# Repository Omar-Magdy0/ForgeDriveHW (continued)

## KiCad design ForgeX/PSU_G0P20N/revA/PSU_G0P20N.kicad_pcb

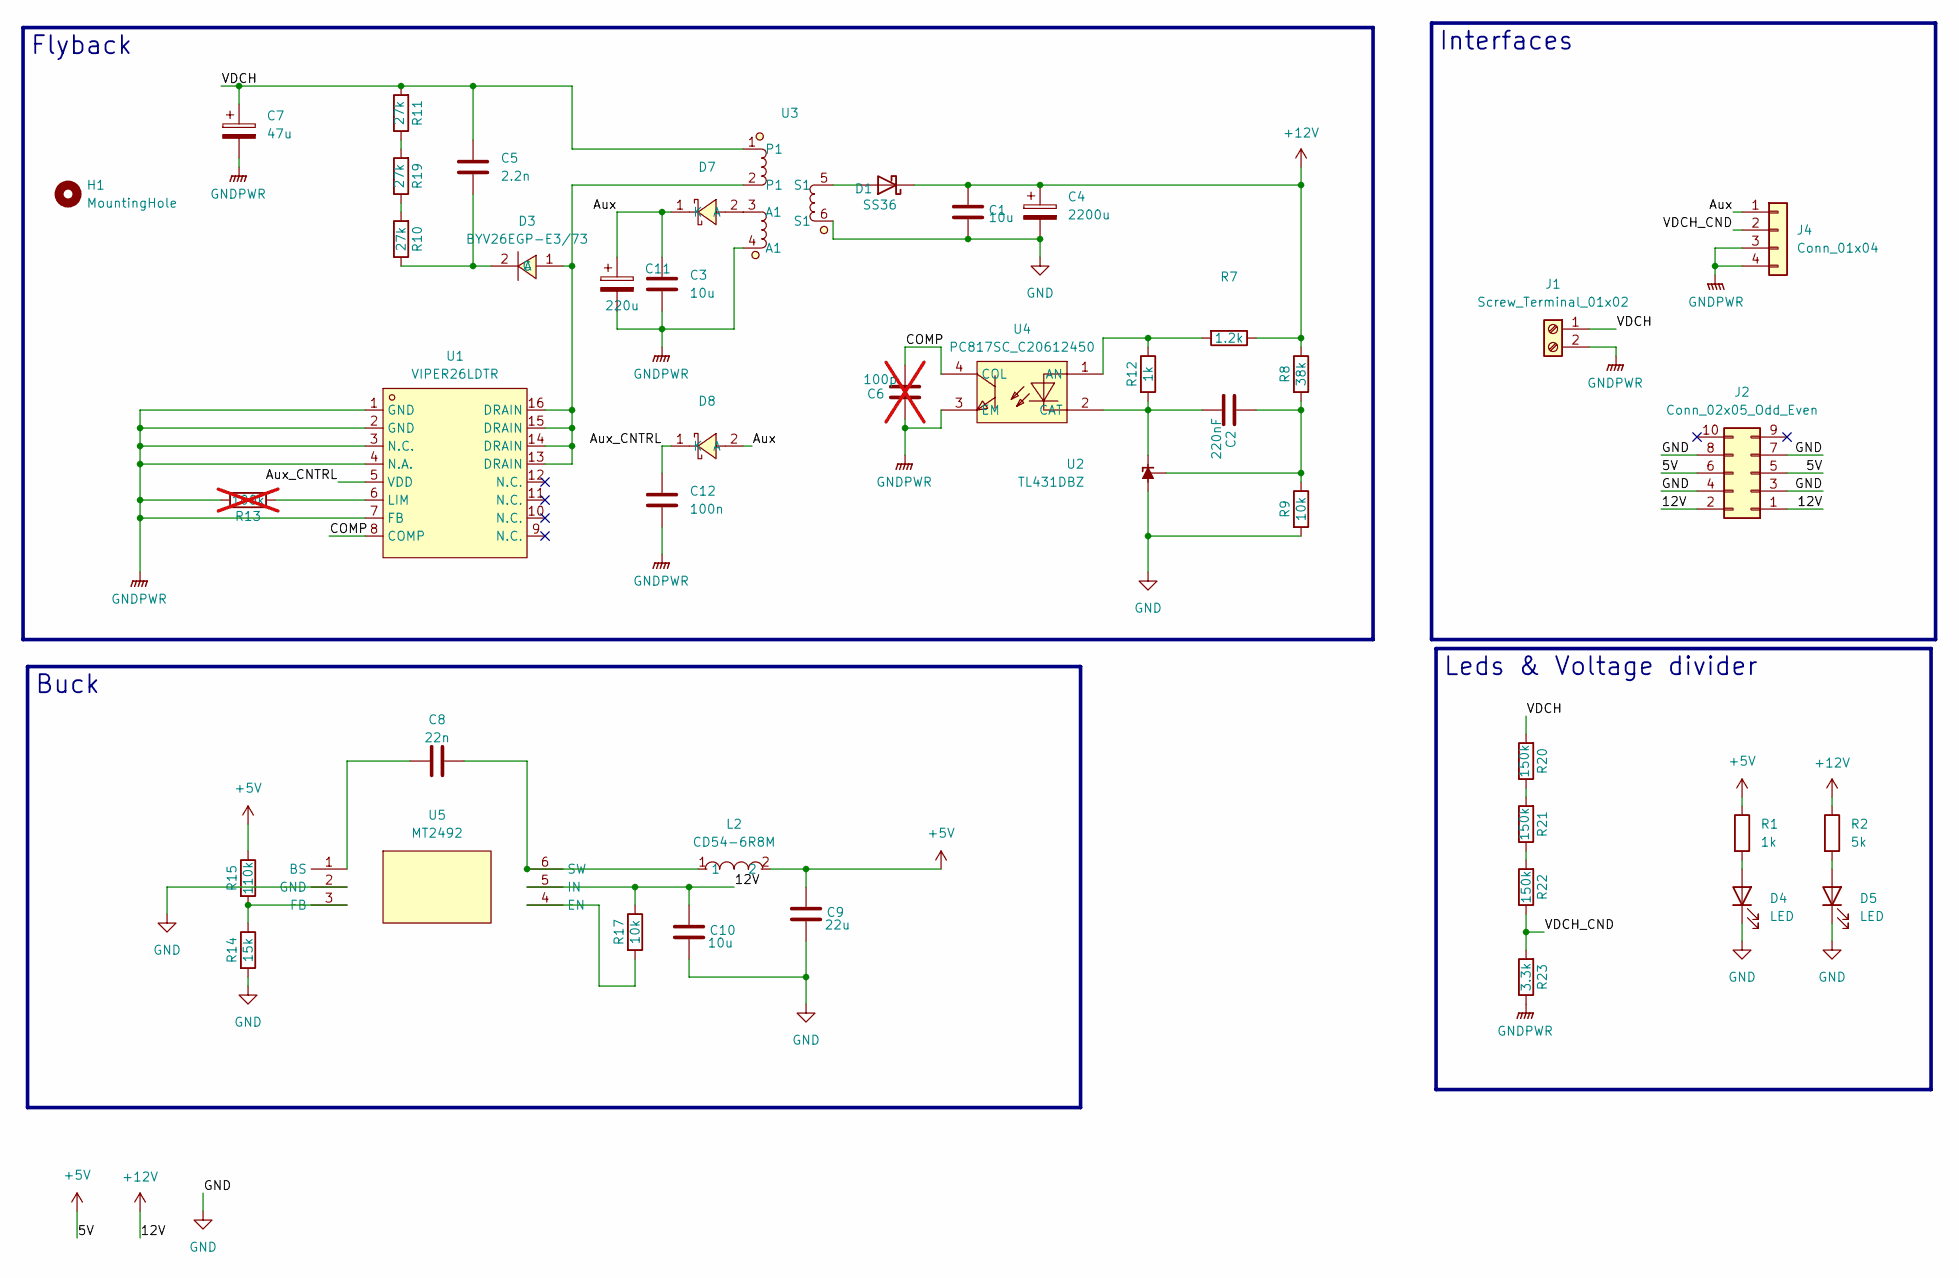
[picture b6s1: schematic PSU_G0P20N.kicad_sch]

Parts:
C1, C3, C10: 10u; C_1206_3216Metric_Pad1.33x1.80mm_HandSolder
C2: 220nF; C_0603_1608Metric_Pad1.08x0.95mm_HandSolder
C4: 2200u; CP_Radial_D10.0mm_P5.00mm
C5: 2.2n; C_Disc_D5.0mm_W2.5mm_P5.00mm
C6: 100p; C_0603_1608Metric_Pad1.08x0.95mm_HandSolder; not fitted
C7: 47u; CP_Radial_D10.0mm_P7.50mm
C8: 22n; C_0603_1608Metric_Pad1.08x0.95mm_HandSolder
C9: 22u; C_1206_3216Metric_Pad1.33x1.80mm_HandSolder
C11: 220u; CP_Radial_D6.3mm_P2.50mm
C12: 100n; C_0603_1608Metric_Pad1.08x0.95mm_HandSolder
D1: SS36; D_SMA
D3: BYV26EGP-E3/73; DO-15_BD3.1-L6.7-P10.70-D0.9-FD; MPN BYV26EGP-E3/73; LCSC Part C15074
D4, D5: LED; LED_1206_3216Metric_Pad1.42x1.75mm_HandSolder
D7, D8: SD103AWS_C5345966; SOD-323_L1.7-W1.3-LS2.5-RD; MPN SD103AWS; LCSC Part C5345966
H1: MountingHole; MountingHole_2.1mm
J1: Screw_Terminal_01x02; SPACER_M3_PCONN_PSU
J2: Conn_02x05_Odd_Even; PinHeader_2x05_P2.54mm_Vertical
J4: Conn_01x04; JST_XH_B4B-XH-A_1x04_P2.50mm_Vertical
L2: CD54-6R8M; IND-SMD_L5.8-W5.2_CD54; MPN CD54-6R8M; LCSC Part C7588992
R1: 1k; R_1206_3216Metric_Pad1.30x1.75mm_HandSolder
R2: 5k; R_1206_3216Metric_Pad1.30x1.75mm_HandSolder
R7: 1.2k; R_0603_1608Metric_Pad0.98x0.95mm_HandSolder
R8: 38k; R_0603_1608Metric_Pad0.98x0.95mm_HandSolder
R9, R17: 10k; R_0603_1608Metric_Pad0.98x0.95mm_HandSolder
R10, R11, R19: 27k; R_1206_3216Metric
R12: 1k; R_0603_1608Metric_Pad0.98x0.95mm_HandSolder
R13: 100k; R_0603_1608Metric_Pad0.98x0.95mm_HandSolder; not fitted
R14: 15k; R_0603_1608Metric_Pad0.98x0.95mm_HandSolder
R15: 110k; R_0603_1608Metric_Pad0.98x0.95mm_HandSolder
R20, R21, R22: 150k; R_1206_3216Metric
R23: 3.3k; R_0603_1608Metric_Pad0.98x0.95mm_HandSolder
U1: VIPER26LDTR; SOIC-16_L9.9-W3.9-P1.27-LS6.0-BL; MPN VIPER26LDTR; LCSC Part C134483
U2: TL431DBZ; SOT-23
U3: E22 Trans
U4: PC817SC_C20612450; OPTO-SMD-4_L4.6-W6.5-P2.54-LS10.3-TL; MPN PC817SC; LCSC Part C20612450
U5: MT2492; SOT-23-6_L2.9-W1.6-P0.95-LS2.8-BL_3; MPN MT2492; LCSC Part C89358

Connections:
+5V: C9.1, J2.5, J2.6, L2.2, R1.1, R15.1
+12V: C1.1, C4.1, C10.1, D1.1 (K), J2.1, J2.2, R2.1, R7.1, R8.1, R17.1, U5.5 (IN)
/Aux: C3.1, C11.1, D7.1 (K), D8.2 (A), J4.1
/Aux_CNTRL: C12.1, D8.1 (K), U1.5 (VDD)
/COMP: C6.2, U1.8 (COMP), U4.4 (COL)
/VDCH: C5.1, C7.1, J1.1, R11.2, R20.2, U3.1
/VDCH_CND: J4.2, R22.1, R23.2
GND: C1.2, C4.2, C9.2, C10.2, D4.1 (K), D5.1 (K), J2.3, J2.4, J2.7, J2.8, R9.2, R14.2, U2.3 (A), U3.6 (S1), U5.2 (GND)
GNDPWR: C3.2, C6.1, C7.2, C11.2, C12.2, J1.2, J4.3, J4.4, R13.1, R23.1, U1.1 (GND), U1.2 (GND), U1.3 (N.C.), U1.4 (N.A.), U1.7 (FB), U3.4 (A1), U4.3 (EM)
unnamed: D1.2 (A), U3.5 (S1)
unnamed: D3.1 (A), U1.13 (DRAIN), U1.14 (DRAIN), U1.15 (DRAIN), U1.16 (DRAIN), U3.2 (P1)
unnamed: C5.2, D3.2 (C), R10.1
unnamed: D4.2 (A), R1.2
unnamed: D5.2 (A), R2.2
unnamed: D7.2 (A), U3.3 (A1)
unnamed: R10.2, R19.1
unnamed: R11.1, R19.2
unnamed: R20.1, R21.2
unnamed: R21.1, R22.2
unnamed: R13.2, U1.6 (LIM)
unnamed: C2.2, R12.2, U2.1 (K), U4.2 (CAT)
unnamed: C2.1, R8.2, R9.1, U2.2 (REF)
unnamed: R7.2, R12.1, U4.1 (AN)
unnamed: C8.2, U5.1 (BS)
unnamed: R17.2, U5.4 (EN)
unnamed: R14.1, R15.2, U5.3 (FB)
unnamed: C8.1, L2.1, U5.6 (SW)

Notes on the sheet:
Flyback
Buck
Interfaces
Leds & Voltage divider

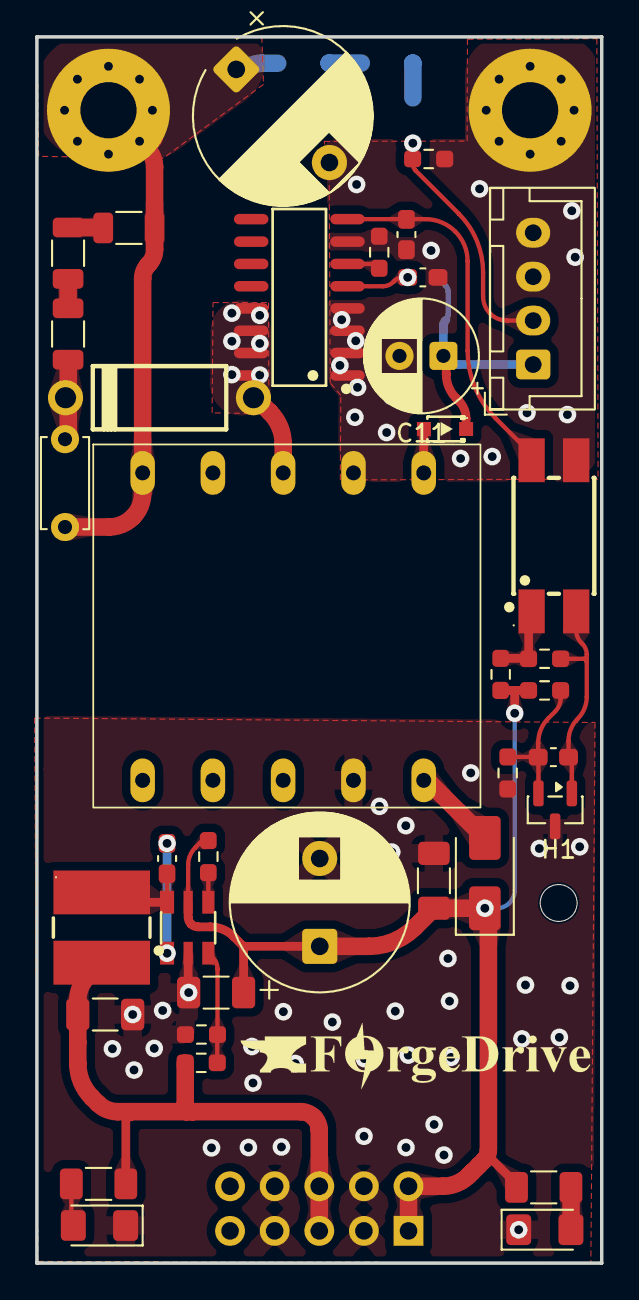
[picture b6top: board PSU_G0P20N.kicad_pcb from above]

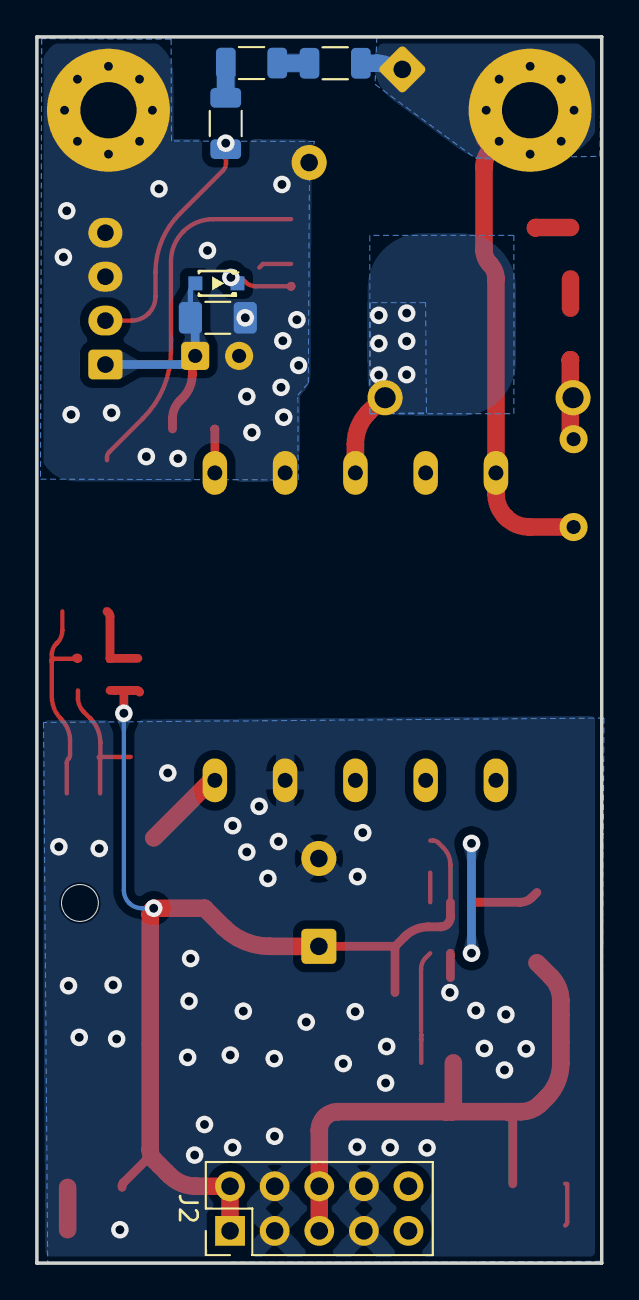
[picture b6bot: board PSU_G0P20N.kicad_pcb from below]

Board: 2 copper layers, 32.1 x 69.8 mm, 45 parts (6 on the bottom side), 27 nets.

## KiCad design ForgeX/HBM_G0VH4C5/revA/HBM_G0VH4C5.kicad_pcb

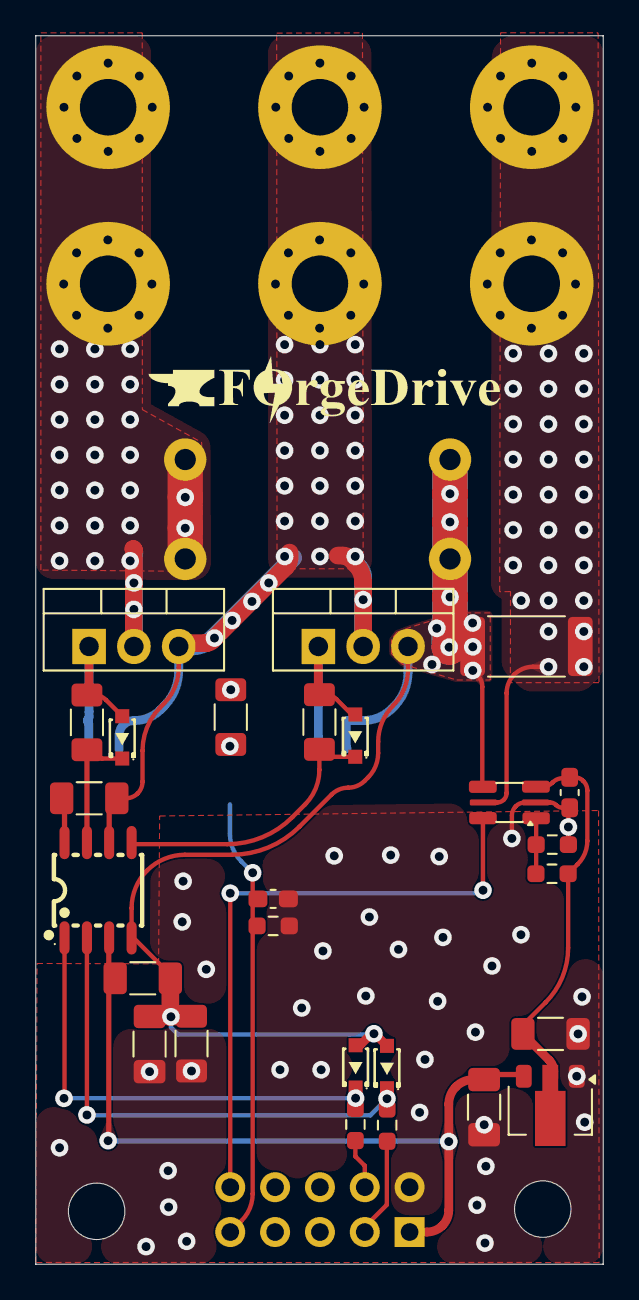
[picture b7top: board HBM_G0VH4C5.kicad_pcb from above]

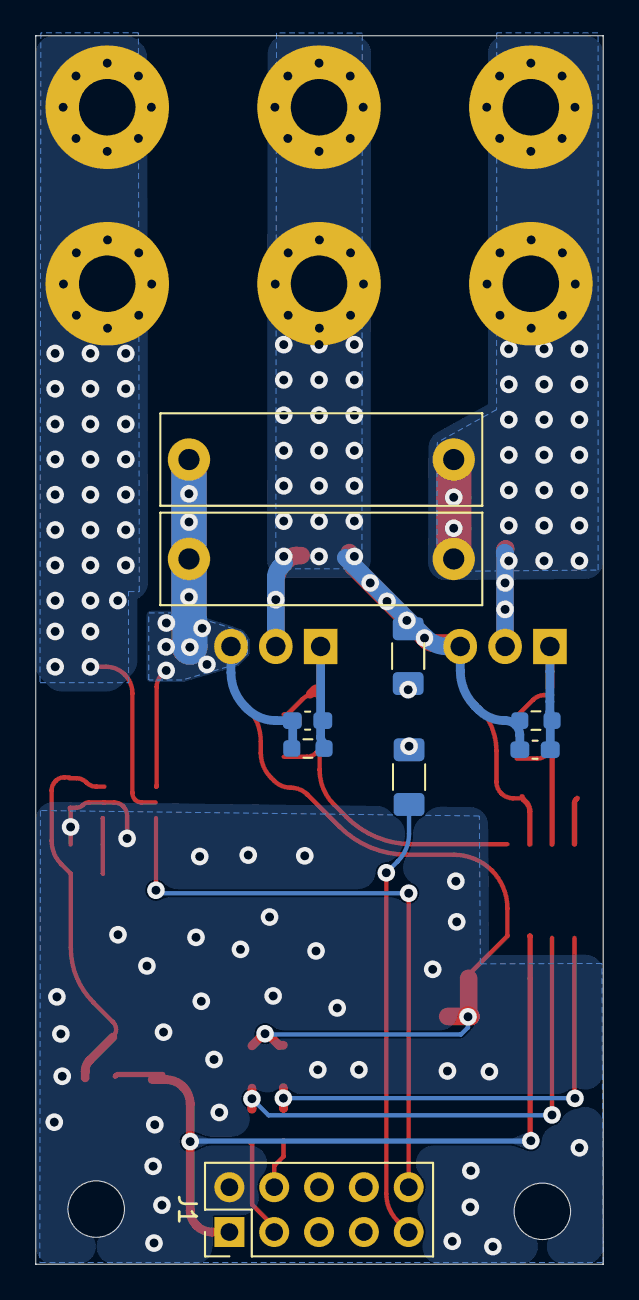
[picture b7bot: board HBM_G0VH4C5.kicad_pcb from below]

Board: 2 copper layers, 32.2 x 69.6 mm, 38 parts (9 on the bottom side), 21 nets.

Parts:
C2, C3: 1n; C_0603_1608Metric_Pad1.08x0.95mm_HandSolder
C4: 0.1u; C_0603_1608Metric_Pad1.08x0.95mm_HandSolder
C7: 10uF; C_1206_3216Metric_Pad1.33x1.80mm_HandSolder
C8: 1u; C_1206_3216Metric_Pad1.33x1.80mm_HandSolder
C9: 47n; C_0603_1608Metric_Pad1.08x0.95mm_HandSolder
C10: 100p; C_1206_3216Metric_Pad1.33x1.80mm_HandSolder
C20, C21: 1u; C_Rect_L18.0mm_W5.0mm_P15.00mm_FKS3_FKP3
C37, C38: 10u; C_1206_3216Metric_Pad1.33x1.80mm_HandSolder
D1, D2, D3, D4: SD103AWS_C5345966; SOD-323_L1.7-W1.3-LS2.5-RD
H1, H2: MountingHole; MountingHole_3.2mm_M3_DIN965
J1: Conn_02x05_Odd_Even; PinHeader_2x05_P2.54mm_Vertical
J2: Screw_Terminal_01x03; SPACER_M3_PCONN_2x03
Q1, Q2: STF24N60M2; TO-220-3_Vertical
R1: 5m; R_2512_6332Metric_Pad1.40x3.35mm_HandSolder
R2, R3, R4, R5: 10k; R_0603_1608Metric_Pad0.98x0.95mm_HandSolder
R6, R7: 1k; R_0603_1608Metric_Pad0.98x0.95mm_HandSolder
R8: 220; R_1206_3216Metric_Pad1.30x1.75mm_HandSolder
R11, R12: 10; R_1206_3216Metric_Pad1.30x1.75mm_HandSolder
R26: 3.3k; R_0603_1608Metric_Pad0.98x0.95mm_HandSolder
R27, R28, R29: 150k; R_1206_3216Metric_Pad1.30x1.75mm_HandSolder
U1: INA199xxDCK; SOT-363_SC-70-6
U3: L6388ED; SO-8_L4.9-W3.9-P1.27-LS5.9-BL
U7: AMS1117-3.3; SOT-89-3

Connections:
+3.3V: C4.1, C38.1, R2.2, U1.3 (V+), U7.2 (VO)
+12V: C7.1, C37.1, J1.1, U3.3 (VCC), U7.3 (VI)
/HS_GateSig: D1.1 (K), R11.1, U3.7 (HVG)
/LS_GateSig: D2.1 (K), R12.1, U3.5 (LVG)
/Shunt+: C2.2, C7.2, C10.1, C20.2, C21.2, D3.2 (A), D4.2 (A), Q1.3 (S), R1.1, R5.1, R8.1, U1.4 (+), U3.4 (GND)
Csense: J1.10, U1.6
GND: C4.2, C9.2, C10.2, C37.2, C38.2, J1.2, R3.1, R8.2, R26.2, U1.2 (GND), U7.1 (GND)
GNDPWR: J2.3, R1.2, U1.5 (-)
HIN: J1.3, R7.1
LIN: J1.4, R6.1
unnamed: C3.1, D1.2 (A), Q2.1 (G), R4.2, R11.2
unnamed: C2.1, D2.2 (A), Q1.1 (G), R5.2, R12.2
unnamed: D3.1 (K), R7.2, U3.2 (HIN)
unnamed: D4.1 (K), R6.2, U3.1 (LIN)
unnamed: R27.2, R28.1
unnamed: R28.2, R29.1
unnamed: R2.1, R3.2, U1.1 (REF)
unnamed: C8.1, U3.8 (VBOOT)
Phase: C3.2, C8.2, J2.2, Q1.2 (D), Q2.3 (S), R4.1, R29.2, U3.6 (OUT)
Phase_Cnd: C9.1, J1.9, R26.1, R27.1
VDCH: C20.1, C21.1, J2.1, Q2.2 (D)
